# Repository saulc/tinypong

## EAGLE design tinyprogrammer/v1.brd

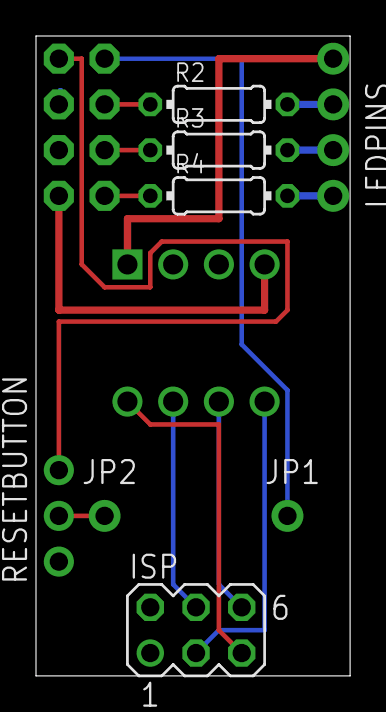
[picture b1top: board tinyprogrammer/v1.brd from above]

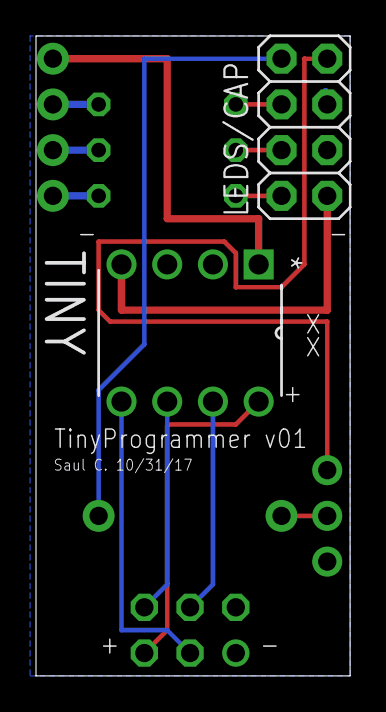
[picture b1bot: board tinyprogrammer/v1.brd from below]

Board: 2 copper layers, 17.4 x 35.5 mm, 10 parts (2 on the bottom side), 15 nets.

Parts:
ISP: MA03-2
JP1, JP2: 1X01-CLEANBIG
LEDPINS: 1X4-CLEANBIG; 1X04-CLEANBIG
LEDS/CAP: 2X04
R2, R3, R4: 0204/7
RESETBUTTON: 1X03-CLEANBIG
TINY: ATTINY85-20PU; DIP254P762X533-8

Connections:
0: ISP.3, TINY.5
1: ISP.6, TINY.6
2: ISP.4, TINY.7
GND: ISP.1, LEDS/CAP.1, LEDS/CAP.3, LEDS/CAP.5, TINY.4
N7: LEDPINS.4, R4.2
N8: LEDPINS.3, R3.2
N9: LEDPINS.2, R2.2
NG: LEDS/CAP.7, RESETBUTTON.3
NR: JP2.1, RESETBUTTON.2
R7: LEDS/CAP.2, R4.1
R8: LEDS/CAP.4, R3.1
R9: LEDS/CAP.6, R2.1
RR: JP1.1, LEDS/CAP.8
RST: LEDPINS.1, TINY.1
VCC: ISP.5, TINY.8

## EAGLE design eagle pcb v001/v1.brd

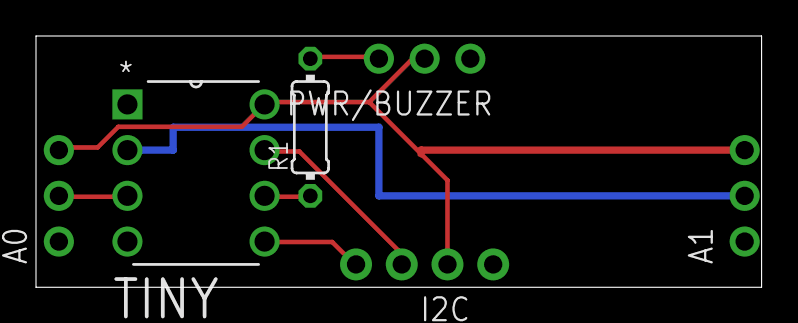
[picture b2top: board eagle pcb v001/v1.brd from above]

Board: 2 copper layers, 40.3 x 14.0 mm, 6 parts (0 on the bottom side), 8 nets.

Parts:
A0, A1: 1X03-CLEANBIG
I2C: 1X4-CLEANBIG; 1X04-CLEANBIG
PWR/BUZZER: 1X03-CLEANBIG
R1: 0204/7
TINY: ATTINY85-20PU; DIP254P762X533-8

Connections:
0: I2C.4, TINY.5
1: R1.1, TINY.6
1OUT: PWR/BUZZER.3, R1.2
2: I2C.3, TINY.7
3: A1.2, TINY.2
4: A0.2, TINY.3
GND: A0.1, A1.1, I2C.1, PWR/BUZZER.1, TINY.4
VCC: A0.3, A1.3, I2C.2, PWR/BUZZER.2, TINY.8

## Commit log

2017-10-30 upload
    working code for tiny pong.
    attiny85/ arduino as isp programmer
2017-10-30 eagle schematic
    created basic part sch
2017-10-30 complete schmatic
    blank board
    branch point for new boards
2017-10-30 completed board v001
    with basic labels.
    fully routed.
    extra wide
2017-10-30 v001 pcb images
    osh park renderings.
    40.34x13.97 mm
    $4.35 for 3
2017-10-30 nothing really.
    resistor size double check. it was fine..
2017-10-31 tinyprogrammer v01
    started a programmer shield for a nano.
2017-10-31 fully routed
    osh park imgs
    3x ordered
2017-11-08 new features
    added buzzer startup sound
    added tinypong splash screen.
    still needs bounce sounds.
